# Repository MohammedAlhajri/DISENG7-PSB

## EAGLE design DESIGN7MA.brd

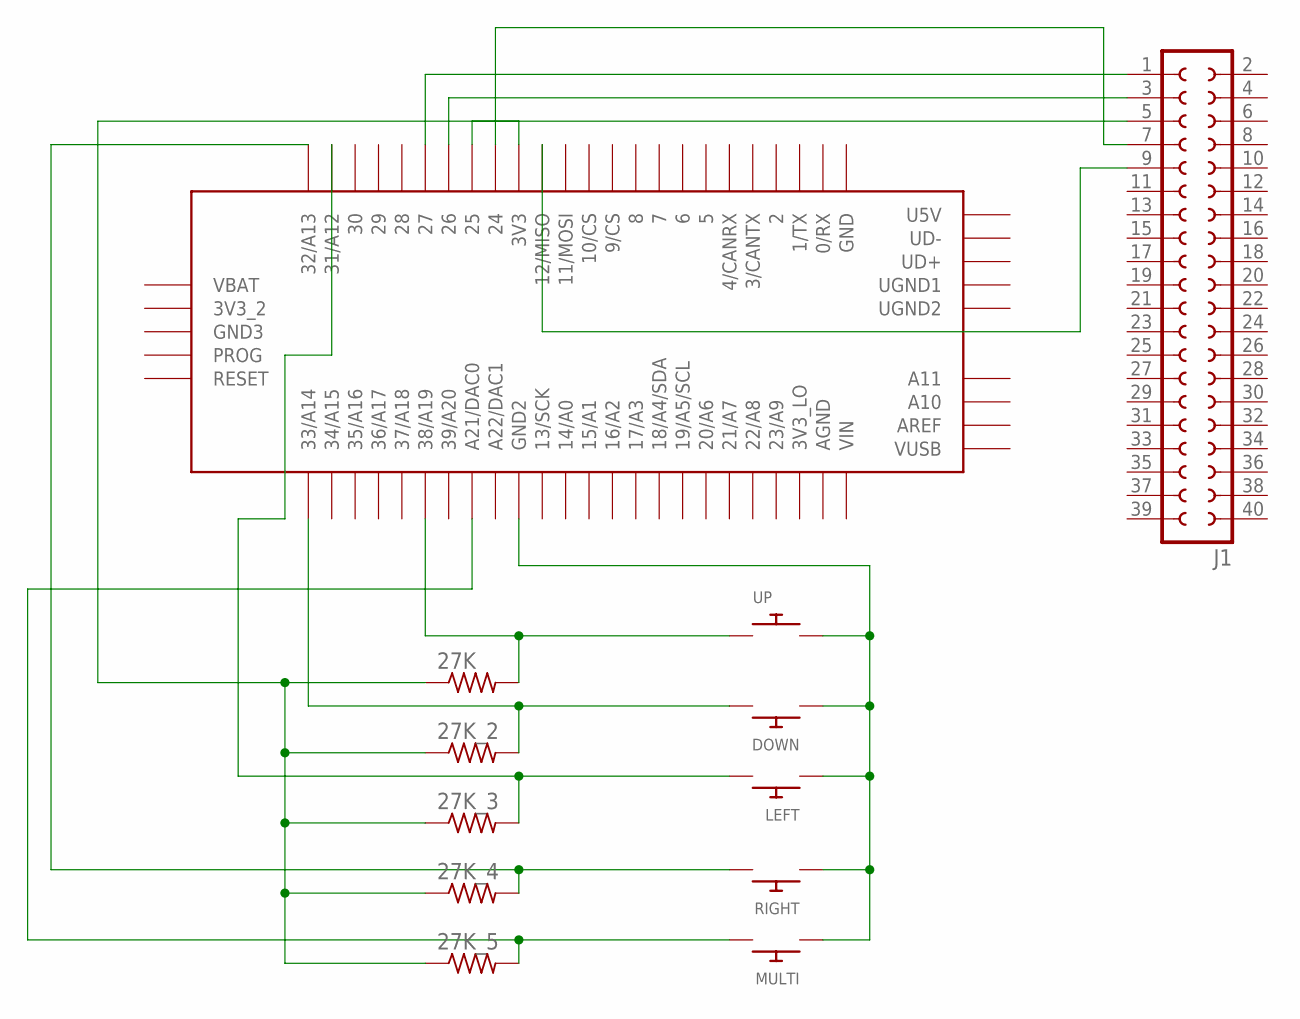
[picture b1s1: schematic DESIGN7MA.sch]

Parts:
27K, 27K_2, 27K_3, 27K_4, 27K_5: R-US_0204/5; 0204/5
DOWN: SWITCH_PUSHBUTTONEVQ-PE; TACT_PANA-EVQ
J1: SOCKET-40V; S40V
LEFT: SWITCH_PUSHBUTTONEVQ-PE; TACT_PANA-EVQ
MULTI: SWITCH_PUSHBUTTONEVQ-PE; TACT_PANA-EVQ
RIGHT: SWITCH_PUSHBUTTONEVQ-PE; TACT_PANA-EVQ
U$1: TEENSY_3.5/3.6
UP: SWITCH_PUSHBUTTONEVQ-PE; TACT_PANA-EVQ

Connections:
unnamed: DOWN.P$1, LEFT.P$1, MULTI.P$1, RIGHT.P$1, U$1.GND2, UP.P$2
unnamed: J1.1, U$1.27
unnamed: 27K_3.2, LEFT.P$2, U$1.31/A12
unnamed: 27K_2.2, DOWN.P$2, U$1.33/A14
unnamed: 27K_4.2, RIGHT.P$2, U$1.32/A13
unnamed: 27K.1, 27K_2.1, 27K_3.1, 27K_4.1, 27K_5.1, U$1.3V3
unnamed: J1.3, U$1.26
unnamed: J1.5, U$1.25
unnamed: J1.7, U$1.24
unnamed: J1.9, U$1.12/MISO
unnamed: 27K_5.2, MULTI.P$2, U$1.21/DAC0 (A21/DAC0)
unnamed: 27K.2, U$1.38/A19, UP.P$1

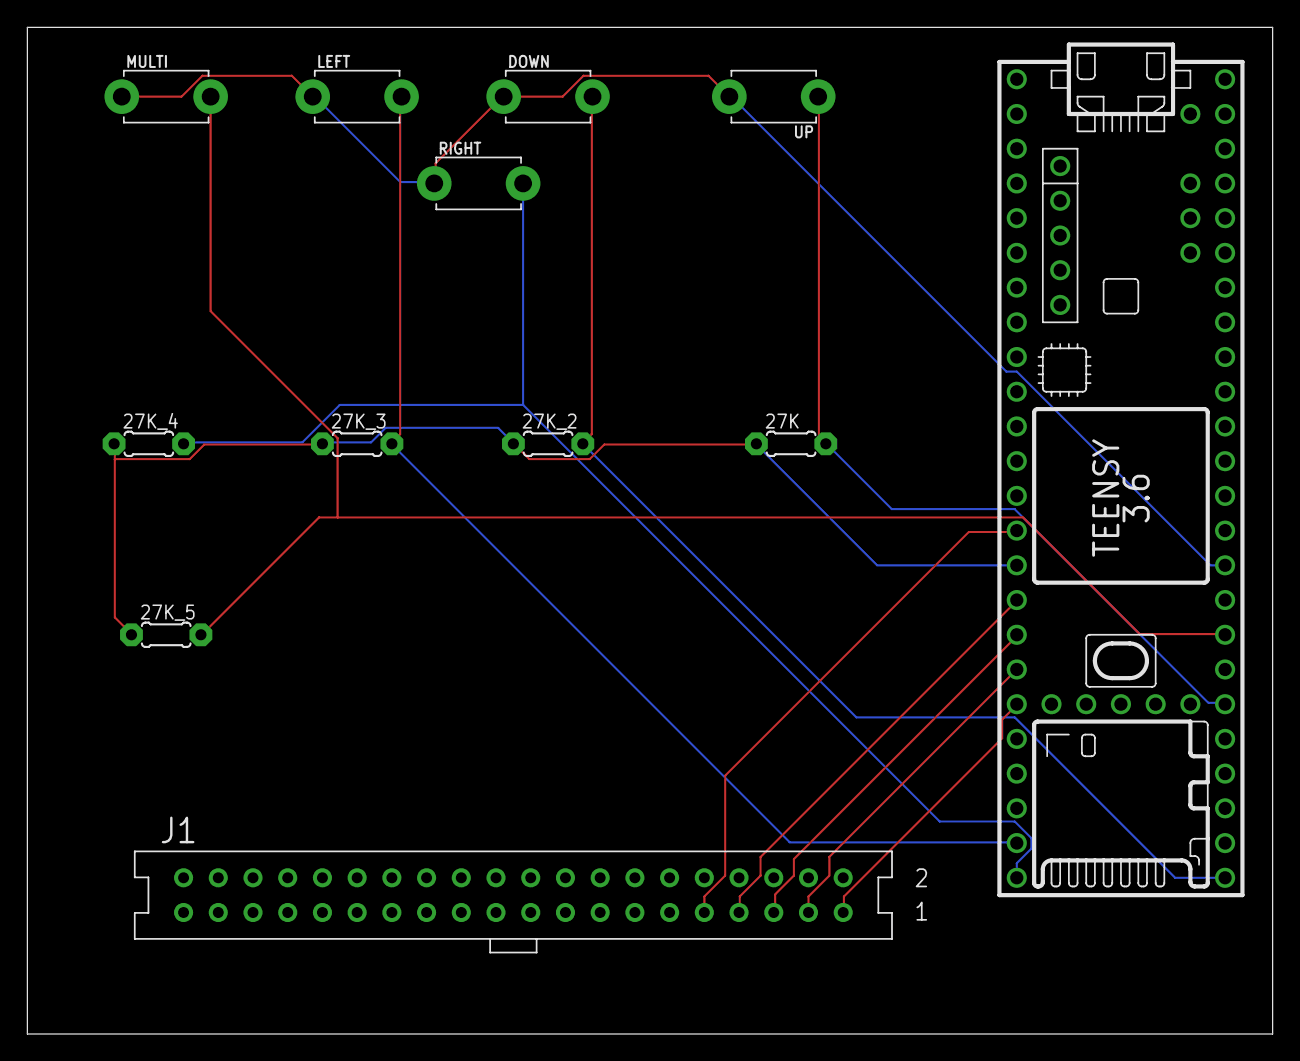
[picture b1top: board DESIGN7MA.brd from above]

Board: 2 copper layers, 91.1 x 73.7 mm, 12 parts (0 on the bottom side), 12 nets.
